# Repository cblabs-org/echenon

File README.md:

# Echenon (`v0.3.0-beta.1`)

**Open-Source Smart Bike Telemetry & FTMS Bridge for the Echelon EX-3 (Passive Tap v1)**

Echenon turns your **Echelon EX-3** indoor bike into an open, self-contained training computer and Bluetooth **FTMS (`0x1826`)** power/cadence bridge that works natively with **Zwift, MyWhoosh, TrainerRoad, Xert EBC, Wahoo SYSTM, and Garmin head units** — without cutting a single factory wire. Ride any app or instructor class while Echenon computes physics-calibrated power, relays your BLE heart-rate monitor, serves a live local web cockpit (`/ride`), and automatically syncs completed `.tcx.gz` activities to **Strava**, **Intervals.icu**, and **Wahoo Cloud**.

---

> [!IMPORTANT]
> ### 🛠️ Looking for Early Beta Builders (`v0.3.0-beta.1` — First Public Beta)
>
> We are recruiting a small cohort of capable DIY makers to build, install, and ride-test the **v1 Passive Tap Board** on their own **Echelon EX-3** bikes.
>
> **Who should join the beta:**
> - You own an **Echelon EX-3** (`ECHEX-3` / `S1001O-A03` console PCB) and want open FTMS telemetry, calibrated virtual power, and automatic cloud ride uploads.
> - You are comfortable soldering through-hole resistors/capacitors onto a `70 × 50 mm` perfboard, crimping 9-pin JST-SM and 3-pin JST connectors, verifying continuity/voltages with a multimeter, and flashing an ESP32-S3 over USB-C using PlatformIO.
> - You are willing to share structured feedback, calibration curves, and diagnostic logs via [GitHub Issues](CONTRIBUTING.md).
>
> 👉 **Start here:** Read the standalone [**v1 Beta Hardware Build & Commissioning Guide (`docs/beta-build-guide.md`)**](docs/beta-build-guide.md).

---

> [!CAUTION]
> ### ⚡ CRITICAL POWER SAFETY: `SW0` Mechanical `VIN` / `USB-C` Interlock
>
> The Echenon v1 Passive Tap Board powers the **Waveshare ESP32-S3-Nano** (`U1`) directly from the bike's `+9 V DC` supply rail (`J1` Pin 8, White) via the board's onboard **MP2322 `VIN` (6–21 V)** regulator (no external buck converter is used).
>
> **Power the ESP32-S3-Nano via bike `+9 V VIN` OR computer `USB-C` — NEVER BOTH SIMULTANEOUSLY.**
> - Always install the mandatory **`SW0` mechanical interlock switch** in series with `J1-8` (`+9 V`) to `U1 VIN`.
> - **Before plugging in USB-C:** Flip `SW0` to **USB / VIN-OFF** (or unplug the bike's 9 V wall adapter).
> - **Before powering the bike on `+9 V`:** Unplug the USB-C cable completely from `U1`, then flip `SW0` to **BIKE / VIN-ON**.
> - See [**`docs/beta-build-guide.md` (Power Interlock Checklist & §5 Pre-Power Sanity Checks)**](docs/beta-build-guide.md) before applying power.

---

## Key Capabilities (Implemented in `v0.3.0-beta.1`)

- **Non-Destructive Inline Passive Tap Harness:** Plugs inline between the EX-3's factory 9-pin JST-SM main loom (`J1 ↔ J2`) and 3-pin JST handlebar encoder loom (`J3 ↔ J4`). Every tap is high-impedance with zero internal GPIO pull-ups/pull-downs — the stock Echelon console and resistance knob continue to work normally, and unplugging the harness restores the bike to 100% stock.
- **First-Principles Calibrated Power Engine (`Physics P3r`):** Computes mechanical watts at 2 Hz from continuous ADC DMA wiper position ($\tilde{p} \in [0, 1]$) and glitch-filtered crank cadence using an electromechanical eddy-current & Kloss induction-rollover model ($R^2 = 0.9995$, $\text{RMSE} = 3.77\text{ W}$ across a 320-point empirical sweep), plus Peloton (`0–100`) braking-curve equivalence and virtual road speed.
- **Per-Bike Calibration Wizard & Live Recalibration UI:** Includes an OLS linear-endpoint **Calibration Wizard** for potentiometer end-stop tolerances, a **Recalibration UI** (`RecalibrationUI`) for fitting reference power readings (`a_scale` + $32 \times 31$ lookup matrix), and custom CSV power-table uploads.
- **Standard BLE FTMS (`0x1826`) + Heart Rate Relay (`0x180D`):**
  - Broadcasts **FTMS Indoor Bike Data (`0x2AD2`)** at 2 Hz (instantaneous power with configurable 0–10 s EMA smoothing, cadence, resistance level `1–32`, virtual speed, and heart rate) for up to 3 simultaneous BLE Central apps (Zwift, MyWhoosh, TrainerRoad, Xert EBC, Wahoo SYSTM, Garmin watches).
  - Connects as a BLE Central (`HRMClient`) to any standard BLE heart-rate strap/armband (including single-connection optical straps like the Echelon Beat `HW901`) and re-broadcasts (`HRMRepeater`) `0x180D` to the Echelon tablet app while embedding HR into FTMS and recorded sessions.
- **Autonomous Ride Recording & Multi-Sink Cloud Sync:**
  - Automatically starts recording on sustained pedalling, buffers 1 Hz anti-aliased `RideRecord` telemetry in 8 MB OPI PSRAM with 30 s LittleFS crash-recovery checkpoints (`/ride_active.bin`), and streams gzipped `.tcx.gz` files (`TCXGenerator`) with 1 Hz `<Watts>` and `<Speed>` extensions.
  - Multi-sink background `UploadQueue` (`IDataSource`) with `BLEManager::ScanInhibit` radio coexistence pushes completed sessions to **Strava** (`StravaUploader`, BYOA OAuth 2.0 — setup guide includes a one-click `/icon-512.png` download of the Concept A app icon, also at [`docs/assets/echenon-icon-512.png`](docs/assets/echenon-icon-512.png)), **Intervals.icu** (`IntervalsIcuUploader`, API key), and **Wahoo Cloud** (`WahooUploader`, BYOA OAuth 2.0), plus optional LittleFS `.ride.gz` persistence (`RidePersistence`).
- **Live Web Cockpit (`/ride`), Portal & JSON-RPC MCP Tools (`/api/mcp`):**
  - **Standalone `/ride` page** (installable as a mobile/tablet split-screen PWA via `/manifest.json` with Concept A `"Telemetry Dial"` icons `/icon-192.png`, `/icon-512.png`, `/favicon.svg`, and `/favicon.ico`) with 2 Hz WebSocket telemetry (`/ws/echenon/live`), rolling 5-minute power chart, HR zones, session start/pause/resume/stop controls, and multi-sink sync prompts (`"Save to device and sync to connected apps"`), backed by `SessionOverlay` REST routes (`/api/session/*`, `/api/upload/*`, `/api/strava/*`, `/api/intervals/*`, `/api/wahoo/*`).
  - **Main Web Portal (`http://echenon.local`)** with live dashboard, Calibration Wizard, Power Tuning, Stored Rides history (`/stored_rides.js`), and Diagnostics event/run viewer (`DiagnosticsRoutes`), protected by **`AuthManager` portal authentication** (`WO-09.1`).
  - **Model Context Protocol (`POST /api/mcp` via `IMCPContributor`):** Exposes structured JSON-RPC tools (`echenon_get_telemetry`, `echenon_calibration`, `echenon_recalibration`, `echenon_upload_power_table`, `echenon_set_ftms_smoothing`, plus `echenon_rig_status` and `echenon_rig_command` when built with `-DWITH_CALIBRATION_RIG` — migrated 100% off legacy HTTP endpoints).

---

## Shopping List & 5-Step Quick Start (`~USD $25–$35`)

### Bill of Materials Summary (v1 Passive Tap Board)

Full circuit schematics, pin-by-pin wire colour tables, and multimeter checklists are in [**`docs/beta-build-guide.md`**](docs/beta-build-guide.md):

| Ref | Part | Qty | Value / Spec | Role |
|---|---|---|---|---|
| `U1` | **Waveshare ESP32-S3-Nano** | 1 | `ESP32-S3R8` (16 MB Flash / 8 MB OPI PSRAM, onboard MP2322 `VIN` 6–21 V regulator) | Main MCU (**no external `U3` buck converter needed**) |
| `SW0` | **Mechanical Interlock Switch** | 1 | SPDT slide/toggle switch rated ≥ 1 A @ 12 V DC (+ optional `D1` `1N5819`/`SS14` Schottky diode) | Series disconnect on `J1-8` (`+9 V`) to `U1 VIN` (**`VIN` OR `USB-C`, never both**) |
| `RS1–RS3` | **22 kΩ Resistors** | 3 | `22 kΩ`, 1% metal film, 1/4 W | High-Z series taps on potentiometer lines (`GPIO 1, 2, 3`) |
| `RS4–RS8` | **4.7 kΩ Resistors** | 5 | `4.7 kΩ`, 1% metal film, 1/4 W | Series protection & RC filter input for cadence (`GPIO 4, 5`) and encoder (`GPIO 8, 9, 10`) |
| `R1a, R2a` | **30 kΩ Resistors** | 2 | `30 kΩ`, 1% metal film, 1/4 W | Upper leg of ÷4 motor-sense dividers (`GPIO 6, 7`) |
| `R1b, R2b` | **10 kΩ Resistors** | 2 | `10 kΩ`, 1% metal film, 1/4 W | Lower leg to `GND` of ÷4 motor-sense dividers (`GPIO 6, 7`) |
| `C1 ×5` | **100 nF Ceramic Capacitors** | 5 | `100 nF` (`0.1 µF`), X7R, ≥ 16 V | Low-pass filter (~338 Hz) & ADC charge reservoir from **ESP32 GPIO side** of `RS4–RS8` to `GND` (`GPIO 4, 5, 8, 9, 10`) |
| `J1 / J2` | **JST-SM 9-Pin Socket + Plug** | 1 pair | 9-pin JST-SM female receptacle (`J1`) + male plug (`J2`) | Main frame-to-console inline pass-through |
| `J3 / J4` | **JST 3-Pin Socket + Plug** | 1 pair | 3-pin JST female receptacle (`J3`) + male plug (`J4`) | Handlebar resistance knob encoder inline pass-through |
| `J5` + Board | **Headers, Perfboard & Wire** | 1 set | `2× 15-pin` `2.54 mm` female socket strips, `70 × 50 mm` FR-4 perfboard, `22 AWG` wire | Carrier board fitting inside the EX-3 console housing |

### Quick Start in 5 Steps

1. **Assemble & Bench-Check the Harness (`U1` Unseated):**
   Follow [**`docs/beta-build-guide.md` (§2–§5)**](docs/beta-build-guide.md) to solder the pass-through looms, resistor/capacitor taps, and `SW0` interlock onto the `70 × 50 mm` perfboard. Complete every unpowered continuity check and live voltage check **before** seating the ESP32-S3-Nano (`U1`) into `J5`.
2. **Clone Repository & Initialize Submodule:**
   ```bash
   git clone --recurse-submodules https://github.com/cblabs-org/echenon.git
   cd echenon
   ```
   *(Note: Echenon builds on the public [`cblabs-org/esp32-app-foundation`](https://github.com/cblabs-org/esp32-app-foundation) submodule (`v1.0.0-beta.2`) under `framework/`.)*
3. **Isolate `VIN` (`SW0` → USB) & Flash Over USB-C:**
   Verify `SW0` is in the **USB / VIN-OFF** position (or the board is unplugged from the bike), seat `U1` into `J5`, connect a USB-C data cable, and flash both the firmware and LittleFS portal image:
   ```bash
   pio run -e ex3-waveshare-nano -t upload
   pio run -e ex3-waveshare-nano -t uploadfs
   ```
4. **WiFi Onboarding & Portal Authentication:**
   Connect to the **`Echenon`** setup WiFi AP (`http://192.168.4.1`), join your 2.4 GHz home WiFi, then open **`http://echenon.local`** and set your administrator password (`AuthManager` protects all configuration, calibration, and ride management routes).
5. **Install in Console, Calibrate & Ride:**
   Unplug the USB-C cable completely, connect `J1 ↔ J2` and `J3 ↔ J4` inline inside the EX-3 console shell, flip `SW0` to **BIKE / VIN-ON**, and power on the bike. Run the **Level Mapping Calibration Wizard** in the portal (`Apps → Level Mapping`), pair your BLE heart-rate monitor (`Bluetooth` tab), configure your connected apps (`Apps → Strava` — using `/icon-512.png` or [`docs/assets/echenon-icon-512.png`](docs/assets/echenon-icon-512.png) when Strava prompts for an app icon — plus `Intervals.icu` and `Wahoo Cloud`), and open **`http://echenon.local/ride`** (or install it as a PWA) or pair `Echenon-XXXX` in Zwift / TrainerRoad / MyWhoosh!

---

## Known Beta Limitations & Roadmap (`v1` → `v2`)

1. **Passive Read-Only Tap in `v1` (No ERG / Active Resistance Control Yet):**
   - The `v1` board is strictly an inline passive observer. You adjust resistance manually with the red handlebar knob while Echenon broadcasts live watts, cadence, resistance level, and heart rate over BLE FTMS (`0x1826`). Closed-loop motor control (`ERG` mode, FTMS Control Point `0x2AD9`, HR-zone auto-resistance, and console-off standalone mode) is planned for the **v2 Active Intercept (MITM) Board**.
2. **`WITH_OTA` Disabled in `v0.3.0-beta.1` (USB-C Updates Only):**
   - Over-the-air firmware updating (`WITH_OTA`) is intentionally disabled in `v0.3.0-beta.1` while upstream framework OTA boot-guard hardening is finalised. All firmware and LittleFS updates during beta are performed over **USB-C with `SW0` flipped to `USB / VIN-OFF`**.
3. **Stock Console Motor Control & Power-Off Best Practice:**
   - Because the stock EX-3 console drives the motor directly in `v1`, stock console firmware quirks remain unchanged (including the stock EX-3 behaviour where unplugging power while parked at a high resistance level can misindex the console's step counter). Echenon detects out-of-range potentiometer travel (`RunawayDetector`) and logs a portal alert, but passive hardware cannot cut motor power. **Best practice:** return the knob to **Level 1** before unplugging the bike.
4. **Verified Bike Model Scope:**
   - Verified on the **Echelon EX-3** (`ECHEX-3` / `S1001O-A03` console PCB). Other Echelon Connect models (EX-1, EX-4s, EX-5, Sport) may share similar harness pinouts but are currently untested — hardware reports and pull requests are welcome!

---

## Documentation Index

| Document | Description |
|---|---|
| [**`docs/beta-build-guide.md`**](docs/beta-build-guide.md) | **Start Here:** Standalone v1 Passive Tap Board BOM, wiring tables, schematics, multimeter checks, USB-C flashing & calibration guide |
| [**`hardware/ex3-waveshare-nano/pcb/`**](hardware/ex3-waveshare-nano/pcb/README.md) | **KiCad 10 PCB Package & Printable Schematics:** [Printable v1 Schematic PDF](hardware/ex3-waveshare-nano/pcb/v1-passive-tap/echenon_v1_passive_tap.pdf), [v1 PCB Layout PDF](hardware/ex3-waveshare-nano/pcb/v1-passive-tap/echenon_v1_passive_tap_pcb.pdf), [v1 Gerbers ZIP](hardware/ex3-waveshare-nano/pcb/gerbers/v1-passive-tap/echenon_v1_passive_tap_gerbers.zip) & Carvera Air CAM runbook |
| [**`SPEC.md`**](SPEC.md) | Canonical Echenon system & firmware specification (v1 Passive & provisional v2 Active architecture) |
| [**`docs/hardware_specification.md`**](docs/hardware_specification.md) | Detailed circuit engineering reference, oscilloscope evidence, impedance analysis & v2 MITM draft notes |
| [**`docs/ex3_specification.md`**](docs/ex3_specification.md) | Echelon EX-3 stock hardware teardown, connector pinouts, actuator cam & sensor electrical profiles |
| [**`docs/power-physics-model.md`**](docs/power-physics-model.md) | First-principles derivation & 320-point empirical verification of the `Physics P3r` eddy-current power model |
| [**`docs/data-sinks.md`**](docs/data-sinks.md) | Multi-sink `UploadQueue` architecture and setup guide for Strava, Intervals.icu, and Wahoo Cloud |
| [**`docs/diagnostics.md`**](docs/diagnostics.md) | PSRAM ring-buffer `DiagnosticsModule` event types and `/api/echenon/events` REST API |
| [**`docs/run-data-persistence.md`**](docs/run-data-persistence.md) | Optional LittleFS `.ride.gz` binary ride storage (`RidePersistence`) and CSV export routes |
| [**`docs/use_case_analysis.md`**](docs/use_case_analysis.md) | Operating scenarios (`UC1`–`UC6`) across Echelon classes, Zwift/FTMS apps, and free rides |
| [**`docs/upstream-ble-without-wifi-assessment.md`**](docs/upstream-ble-without-wifi-assessment.md) | Assessment & upstream issue draft for BLE peripheral/central operation without WiFi STA |
| [**`CONTRIBUTING.md`**](CONTRIBUTING.md) | Beta bug reporting guidelines, secret-scrubbing checklist, build environments & developer workflow |
| [**`CHANGELOG.md`**](CHANGELOG.md) | Release history and `v0.3.0-beta.1` capability summary |
| [**`LICENSE`**](LICENSE) | Apache License 2.0 and third-party MIT attribution notices |

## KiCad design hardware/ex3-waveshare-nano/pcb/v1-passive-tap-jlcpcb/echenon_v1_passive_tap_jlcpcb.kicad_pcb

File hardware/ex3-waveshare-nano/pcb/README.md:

# Echenon PCB Fabrication Package (`ex3-waveshare-nano`)

**KiCad 10** PCB projects, **Makera Carvera Air** home-CNC bundles, and **JLCPCB 2-Layer SMD PCBA** turnkey assembly bundles for the Echenon hardware ([beta-build-guide.md](../../../docs/beta-build-guide.md), [hardware_specification.md](../../../docs/hardware_specification.md), [board.h](../board.h)).

- **Deliverables A & B (Carvera Air Home CNC):** **100% single-sided bottom-copper (`B.Cu`)** through-hole layouts — zero copper via rivets, zero double-sided board flips, and zero inaccessible solder joints beneath `J5` headers.
- **Deliverable C (JLCPCB 2-Layer SMD PCBA — Hybrid Carrier):** **2-layer FR-4 (`F.Cu` + solid `B.Cu` ground plane)** layout where JLCPCB factory-populates all **18 surface-mount passives + Schottky diode** using **100% \$0-setup JLCPCB Basic Parts**, leaving only the `2.54 mm` headers/pigtails (`J1–J4`, `SW0`, `U1` socket) for quick bench soldering.

---

## 1. Repository Layout

| Path | Purpose | Dimensions | Status |
|---|---|---|---|
| [generate_pcbs.py](generate_pcbs.py) | Deterministic KiCad 10 S-expression generator + `kicad-cli` ERC/DRC, Gerber, BOM/CPL, 3D PNG, SVG & PDF runner | — | Verified |
| [coupon/](coupon/) | **Deliverable A:** Carvera Air calibration test coupon (`carvera_calibration_coupon.kicad_*`, [schematic PDF](coupon/carvera_calibration_coupon.pdf), [PCB PDF](coupon/carvera_calibration_coupon_pcb.pdf)) | `25 × 20 mm` | ERC=0, DRC=0 |
| [v1-passive-tap/](v1-passive-tap/) | **Deliverable B:** Carvera Air v1 Passive Tap Board (`echenon_v1_passive_tap.kicad_*`, [schematic PDF](v1-passive-tap/echenon_v1_passive_tap.pdf), [PCB PDF](v1-passive-tap/echenon_v1_passive_tap_pcb.pdf)) | `70 × 50 mm` | ERC=0, DRC=0 |
| [v1-passive-tap-jlcpcb/](v1-passive-tap-jlcpcb/) | **Deliverable C:** JLCPCB 2-Layer SMD PCBA v1 Passive Tap Board (`echenon_v1_passive_tap_jlcpcb.kicad_*`, [schematic PDF](v1-passive-tap-jlcpcb/echenon_v1_passive_tap_jlcpcb.pdf), [PCB PDF](v1-passive-tap-jlcpcb/echenon_v1_passive_tap_jlcpcb_pcb.pdf)) | `70 × 50 mm` | ERC=0, DRC=0, SMD=18 |
| [gerbers/coupon/](gerbers/coupon/) | Ready-to-mill Gerbers, Excellon drills, [`carvera_calibration_coupon_gerbers.zip`](gerbers/coupon/carvera_calibration_coupon_gerbers.zip), SVGs | `25 × 20 mm` | 2 drills (`0.9`, `1.0 mm`) |
| [gerbers/v1-passive-tap/](gerbers/v1-passive-tap/) | Ready-to-mill Gerbers, Excellon drills, [`echenon_v1_passive_tap_gerbers.zip`](gerbers/v1-passive-tap/echenon_v1_passive_tap_gerbers.zip), SVGs | `70 × 50 mm` | 2 drills (`0.9`, `1.0 mm`) |
| [gerbers/v1-passive-tap-jlcpcb/](gerbers/v1-passive-tap-jlcpcb/) | Turnkey JLCPCB bundle: [`echenon_v1_passive_tap_jlcpcb_gerbers.zip`](gerbers/v1-passive-tap-jlcpcb/echenon_v1_passive_tap_jlcpcb_gerbers.zip), [`_bom.csv`](gerbers/v1-passive-tap-jlcpcb/echenon_v1_passive_tap_jlcpcb_bom.csv), [`_cpl.csv`](gerbers/v1-passive-tap-jlcpcb/echenon_v1_passive_tap_jlcpcb_cpl.csv), [3D Top PNG](gerbers/v1-passive-tap-jlcpcb/echenon_v1_passive_tap_jlcpcb_3d_top.png), [3D Bottom PNG](gerbers/v1-passive-tap-jlcpcb/echenon_v1_passive_tap_jlcpcb_3d_bottom.png) | `70 × 50 mm` | 2-Layer + Economic PCBA |

---

## 2. Carvera Air CNC Design Rules (Built Into Both Boards)

- **Copper Layer:** `B.Cu` only (no `F.Cu` tracks, no vias).
- **Minimum Track Width:** `0.50 mm` signals (`0.60–0.90 mm` for motor sense pass-throughs, `GND`, and `+9 V`).
- **Minimum Copper Clearance:** `0.45 mm` everywhere (sized for `0.2 mm 30°` V-bits with 2–3 isolation passes).
- **Standardized Tooling (Only 2 Drill Sizes):**
  - `T1 = 0.90 mm`: Axial resistors (`RS1–RS8`, `R1a/b`, `R2a/b`), Schottky diode (`D1`), ceramic capacitors (`C1_1–C1_5`).
  - `T2 = 1.00 mm`: Waveshare ESP32-S3-Nano socket headers (`J5` / `U1`), pigtail solder pads (`J1–J4`), and `SW0` interlock pins.
  - `0.80 mm` corn endmill (`Edge.Cuts`): Board perimeter, corner `M2.5` mounting holes (`2.70 mm` dia), and pigtail strain-relief tie holes (`2.20 mm` dia) — milled automatically on the contour pass with zero extra drill bits.

---

## 3. Deliverable A: Calibration Coupon (`25 × 20 mm`)

Mill the coupon first in the corner of a **single-sided blank** (`100 × 150 mm`) to dial in your V-bit cut depth and drill fit before cutting the full `70 × 50 mm` board:

- Tests one `÷4` motor-sense divider cell (`R_DIV1 30 kΩ`, `R_DIV2 10 kΩ`) + `C_FILT1 100 nF` cap + `J_LOOM1` (`1×2` pigtail pads) + `J_TEST1` (`1×3` Nano socket strip) + one `2.2 mm` strain-relief hole.
- **Check after milling:**
  1. Confirm `0.50 mm` & `1.00 mm` copper traces are crisp with clean isolation channels and no copper whiskers.
  2. Test-fit your `2.54 mm` female socket strip into `J_TEST1` (`1.00 mm` holes), `1/4 W` axial resistor leads into `R_DIV1` (`0.90 mm` holes), and stripped `22 AWG` JST pigtail wire into `J_LOOM1` (`1.00 mm` holes).

---

## 4. Deliverable B: Echenon v1 Passive Tap Board (`70 × 50 mm`)

Matches the DR-1 frozen schematic in [beta-build-guide.md](../../../docs/beta-build-guide.md) and [board.h](../board.h):

- **Top-Side Component Placement (`F.SilkS`):**
  - `J4` (Console) ↔ `J3` (Resistance Knob), 3-pin JST pigtail banks (`1: Black ENC_CHA`, `2: Orange/Yellow ENC_VCC`, `3: Red ENC_CHB`).
  - `J2` (Console) ↔ `J1` (Bike Frame), 9-pin JST-SM pigtail banks (`1: Red MOT+`, `2: Black MOT−`, `3: Yellow POT_HI`, `4: Blue POT_WIPER`, `5: Green POT_LO`, `6: Orange CAD`, `7: Grey CAD_RTN`, `8: White +9V`, `9: Brown GND`).
  - **Strain Relief:** Loop a small nylon zip-tie through the `2.2 mm` holes beside `J1/J2` and `J3/J4` around each pigtail cable jacket so pulling the plugs never stresses the solder joints.
  - **`SW0` Physical USB-C Blocker (`x = 4.80 mm`):** Mount a `2-pin` header or socket/jumper block straddling the USB-C port entrance of `U1`. When the `+9 V` bridge jumper is installed across `SW0`, it **physically blocks insertion of a USB-C cable**.
  - **`D1` (`1N5819` Schottky Diode):** Bridges vertically over the bottom `A0–A3` tracks (`Pad 1` square cathode toward `U1` `VIN`, `Pad 2` round anode toward `SW0`). Match the diode silver/white cathode band to the square pad!
  - **Reserved Pins Left Unconnected:** `U1` `D8` (`GPIO 17`), `D1/TX1` (`GPIO 43`), `D0/RX0` (`GPIO 44`).
- **Schematics & Off-Board Reference Circuitry:** Both schematics use official KiCad 10 IEC symbols (`Device:R`, `Device:C`, `Device:D_Schottky`, `Switch:SW_SPST`, `Connector_Generic:Conn_01x*`, `power:GND`) with continuous wired dividers, RC filters, and harnesses. [echenon_v1_passive_tap.kicad_sch](v1-passive-tap/echenon_v1_passive_tap.kicad_sch) also includes dashed off-board EX-3 bike and stock console reference blocks (`M1`, `RV1`, `SW_CAD1`, `PS1`, `ENC1`, `CON1`) marked `on_board no`, `in_bom no`, and `in_pos_files no` so end-to-end signal flow is documented without entering the PCB or BOM.

---

## 5. Makera CAM & Carvera Air Production Runbook

### Step 1: Stock Setup
1. Secure a clean **single-sided copper-clad blank (`100 × 150 mm`)** **copper-side UP** onto your Carvera Air wasteboard/sub-spoiler using flat double-sided tape across the full underside (essential so the board does not vibrate or lift during V-bit isolation).
2. Register the lower-left corner against the L-bracket origin.
3. Put **bit collars** on your 4 tools (matching your Makera PCB Fabrication Pack):
   - **Isolation:** `1/8"` `0.2 mm 30°` V-bit (or `0.1 mm 60°` V-bit)
   - **Drill 1:** `0.90 mm` PCB drill bit
   - **Drill 2:** `1.00 mm` PCB drill bit
   - **Contour / Cutout:** `0.80 mm` corn endmill

### Step 2: Import & Mirror in Makera CAM (CRITICAL FOR SINGLE-SIDED `B.Cu`)
1. Open **Makera CAM** → create a **3-Axis Project**.
2. Click **Import PCB** and select the unzipped Gerbers + `.drl` files from [gerbers/coupon/](gerbers/coupon/) or [gerbers/v1-passive-tap/](gerbers/v1-passive-tap/) (`*-bottom_layer.gbl`, `*-B_Mask.gbs`, `*-Edge_Cuts.gm1`, `*-PTH.drl`).
3. **CRITICAL — Mirror Together Before Generating Toolpaths:**
   - Standard KiCad `B.Cu` Gerbers and `.drl` files are exported in **top-down X-ray coordinates**, whereas your single-sided copper blank sits **copper-side UP** on the Carvera bed.
   - Select **all imported PCB layers together** (`B.Cu`, `B.Mask`, `Edge.Cuts`, `PTH.drl`) → **Adjust Object → Mirror (Horizontal / across Y-axis around Stock Center)**.
   - **Visual Sanity Check (Do Not Skip!):** Compare the Makera CAM workspace view against the mirrored bottom-copper preview SVG:
     - Coupon: [gerbers/coupon/carvera_calibration_coupon_bottom_copper.svg](gerbers/coupon/carvera_calibration_coupon_bottom_copper.svg) (`J_LOOM1` on top-right, strain-relief hole on top-right corner).
     - v1 Board: [gerbers/v1-passive-tap/echenon_v1_passive_tap_bottom_copper.svg](gerbers/v1-passive-tap/echenon_v1_passive_tap_bottom_copper.svg) (**`SW0` on the RIGHT**, **`J1/J2` 9-pin bank on the TOP-LEFT**, **`J3/J4` 3-pin bank on the TOP-RIGHT**, and `ECHENON v1 B.Cu` text readable left-to-right).

### Step 3: Toolpaths & Milling Parameters
1. **Isolation Routing (`*-bottom_layer.gbl`):**
   - Bit: `0.2 mm 30°` V-bit (`12,000–13,000 RPM`, feed `150–250 mm/min`, plunge `60 mm/min`).
   - Cut depth: `-0.08 mm` to `-0.10 mm` (`1 oz` copper is `0.035 mm` thick; `0.08 mm` cleanly cuts through copper + minor surface variation without digging deep into substrate).
   - Isolation passes: **2–3 passes** (`~0.25–0.35 mm` total moat width; our `0.45 mm` minimum DRC clearance gives plenty of margin).
2. **Drilling (`*-PTH.drl`):**
   - `T1 = 0.90 mm` (`10,000 RPM`, plunge `120–150 mm/min`, depth `-1.85 mm` for `1.5 mm` FR-4/FR-1 blank).
   - `T2 = 1.00 mm` (same speed/feed/depth).
3. **Contour & Mounting/Strain-Relief Holes (`*-Edge_Cuts.gm1`):**
   - Bit: `0.80 mm` corn endmill (`10,000–12,000 RPM`, `2–3` step-downs to `-1.85 mm` depth, feed `150–200 mm/min`).
   - Add **4 small holding tabs** (`1.5 mm` wide × `0.6 mm` high) on the outer board rectangle (not inside the mounting/strain-relief circles).

### Step 4: Carvera Controller Execution & Safety
1. Enable **Auto-Leveling (`G32` wireless Z-probe mesh)** across the PCB bounding box (e.g., `5 × 4` or `7 × 5` grid points) before cutting traces.
2. Follow **Carvera Controller** prompts during **`M6` Quick Tool Changes** (each bit swap automatically runs the tool-length offset setter).
3. **Dust Safety (especially for FR-4 blanks):**
   - Keep the Carvera Air enclosure closed and run vacuum extraction throughout the cut.
   - Wear an N95/P100 mask when opening the lid, **never** use compressed air, and wipe the finished board and bed clean with a damp paper towel or isopropyl alcohol (IPA) wipe.
4. *(Optional)* **UV Solder Mask (Final Bike Board Only):** Skip UV mask on your first test board so every trace is easy to inspect and probe. For the final bike-installed board, roll a thin coat of UV solder mask onto the copper side, cure under the `365 nm` lamp, and run Makera CAM's pad-clearing pass from `*-B_Mask.gbs` using the spring-loaded mask removal bit.

---

## 6. Post-Mill Pre-Power Verification (With `U1` Unseated!)

Before inserting the **Waveshare ESP32-S3-Nano** (`U1`) into `J5`:
1. Visually inspect all isolation moats under bright light/magnifier and scrub lightly with Scotch-Brite/IPA to remove any fine copper burrs.
2. Buzz out continuity on all 12 straight pass-through pins (`J1-1..9 ↔ J2-1..9`, `J3-1..3 ↔ J4-1..3`).
3. Verify **zero continuity (open circuit)** between adjacent pads and between `+9 V` (`J1-8`), `VIN` (`U1-30`), and `GND` (`J1-9`).
4. Solder `RS1–RS8`, `R1a/b`, `R2a/b`, `C1_1–C1_5`, `D1`, `SW0`, `J5` headers, and `J1–J4` pigtails.
5. **Interlock Check:** With `U1` still unseated, apply `+9 V` to `J1-8`/`J1-9`:
   - `SW0` **OPEN (USB position):** `0.0 V` at `U1` `VIN` (`Pad 30`).
   - `SW0` **BRIDGED (BIKE position):** `~8.6–8.7 V` at `U1` `VIN` (`Pad 30`, accounting for `D1` `~0.35 V` Schottky drop), and USB-C port physically blocked.
6. Proceed with [beta-build-guide.md §5–§7](../../../docs/beta-build-guide.md) to seat `U1` and commission on the EX-3.

---

## 7. Deliverable C: JLCPCB 2-Layer SMD PCBA Edition (`70 × 50 mm`)

[v1-passive-tap-jlcpcb/](v1-passive-tap-jlcpcb/) implements the identical DR-1 frozen circuit as a **2-layer FR-4 (`1.6 mm`) Hybrid SMD Carrier**:

- **2-Layer Signal Integrity:** Top-side (`F.Cu`) `0805`/`SMA` SMD placement over an unbroken thermal-relieved **`B.Cu` `GND` ground plane** with dedicated ground vias right beside every `100 nF` RC filter capacitor (`C1_1–C1_5`) and `÷4` divider leg (`R1b`, `R2b`).
- **Optical & Mechanical Features:** 3 asymmetric `1.0 mm` optical fiducials (`FID1–FID3`, `>= 5 mm` from edges), 4 corner `M2.5` (`2.70 mm` NPTH) mounting holes (`MH1–MH4`), and 3 `2.20 mm` NPTH zip-tie strain-relief holes (`SR1–SR3`). All 18 SMD components sit well inside JLCPCB's `5 mm` conveyor rail margin.
- **100% JLCPCB Basic Parts (\$0 Feeder Setup Fee on Economic PCBA):**

| Designators | Value / Spec | Package | MPN | JLCPCB Part # | Tier | Qty |
|---|---|---|---|---|---|---|
| `RS4–RS8` | `4.7 kΩ` ±1% 1/8W | `0805` | `0805W8F4701T5E` | **`C17673`** | Basic | 5 |
| `R1b, R2b` | `10 kΩ` ±1% 1/8W | `0805` | `0805W8F1002T5E` | **`C17414`** | Basic | 2 |
| `RS1–RS3` | `22 kΩ` ±1% 1/8W | `0805` | `0805W8F2202T5E` | **`C17560`** | Basic | 3 |
| `R1a, R2a` | `30 kΩ` ±1% 1/8W | `0805` | `0805W8F3002T5E` | **`C17621`** | Basic | 2 |
| `C1_1–C1_5` | `100 nF` 50V X7R | `0805` | `CL21B104KBCNNNC` | **`C49678`** | Basic | 5 |
| `D1` | `SS14` 40V 1A Schottky | `SMA (DO-214AC)` | `SS14` | **`C2480`** | Basic | 1 |

### JLCPCB Ordering Steps
1. Go to [jlcpcb.com](https://jlcpcb.com) → **Order Now** → upload [`echenon_v1_passive_tap_jlcpcb_gerbers.zip`](gerbers/v1-passive-tap-jlcpcb/echenon_v1_passive_tap_jlcpcb_gerbers.zip).
2. Keep standard 2-layer defaults (`FR-4`, `2 Layers`, `1.6 mm` thickness, `1 oz` copper, `HASL (with lead)` or `LeadFree HASL` / `ENIG`, `5 pcs`).
3. Scroll down and toggle **PCB Assembly** → **ON**:
   - **PCBA Type:** `Economic`
   - **Assembly Side:** `Top Side`
   - **PCBA Qty:** `2` (or `5` to populate the entire batch)
4. Click **Next**, then upload:
   - **BOM File:** [`echenon_v1_passive_tap_jlcpcb_bom.csv`](gerbers/v1-passive-tap-jlcpcb/echenon_v1_passive_tap_jlcpcb_bom.csv)
   - **CPL File:** [`echenon_v1_passive_tap_jlcpcb_cpl.csv`](gerbers/v1-passive-tap-jlcpcb/echenon_v1_passive_tap_jlcpcb_cpl.csv)
5. **DFM / Polarity Sanity Check (10 seconds):** On JLCPCB's 2D/3D component placement preview, confirm that **`D1` (`SS14`)** has its cathode band facing **LEFT** over the **`K`** silkscreen bar (matching [echenon_v1_passive_tap_jlcpcb_3d_top.png](gerbers/v1-passive-tap-jlcpcb/echenon_v1_passive_tap_jlcpcb_3d_top.png)). If a reel change ever flips `D1`, click `D1` in the preview and rotate `180°`.
6. **Bench Finish Upon Arrival (~5 minutes):** Solder the `2×15` `2.54 mm` female socket strips (`U1`), the `2-pin` USB-C blocker header/jumper (`SW0`), and either `2.54 mm` headers or pre-wired JST pigtails (`J1–J4`). Run the `SW0` interlock check in §6 Step 5 before seating your Waveshare ESP32-S3-Nano!

---

## 8. Regenerating After Changes

```bash
python3 hardware/ex3-waveshare-nano/pcb/generate_pcbs.py
```

The script regenerates all three KiCad 10 projects (`coupon`, `v1-passive-tap`, `v1-passive-tap-jlcpcb`), runs headless `kicad-cli sch erc` and `kicad-cli pcb drc --schematic-parity --severity-all` (with automatic `B.Cu` zone filling), verifies 1-to-1 BOM/CPL designator parity, and rebuilds all Gerbers, drill files, CSVs, 3D PNG renders, SVGs, printable PDFs, and `.zip` archives.

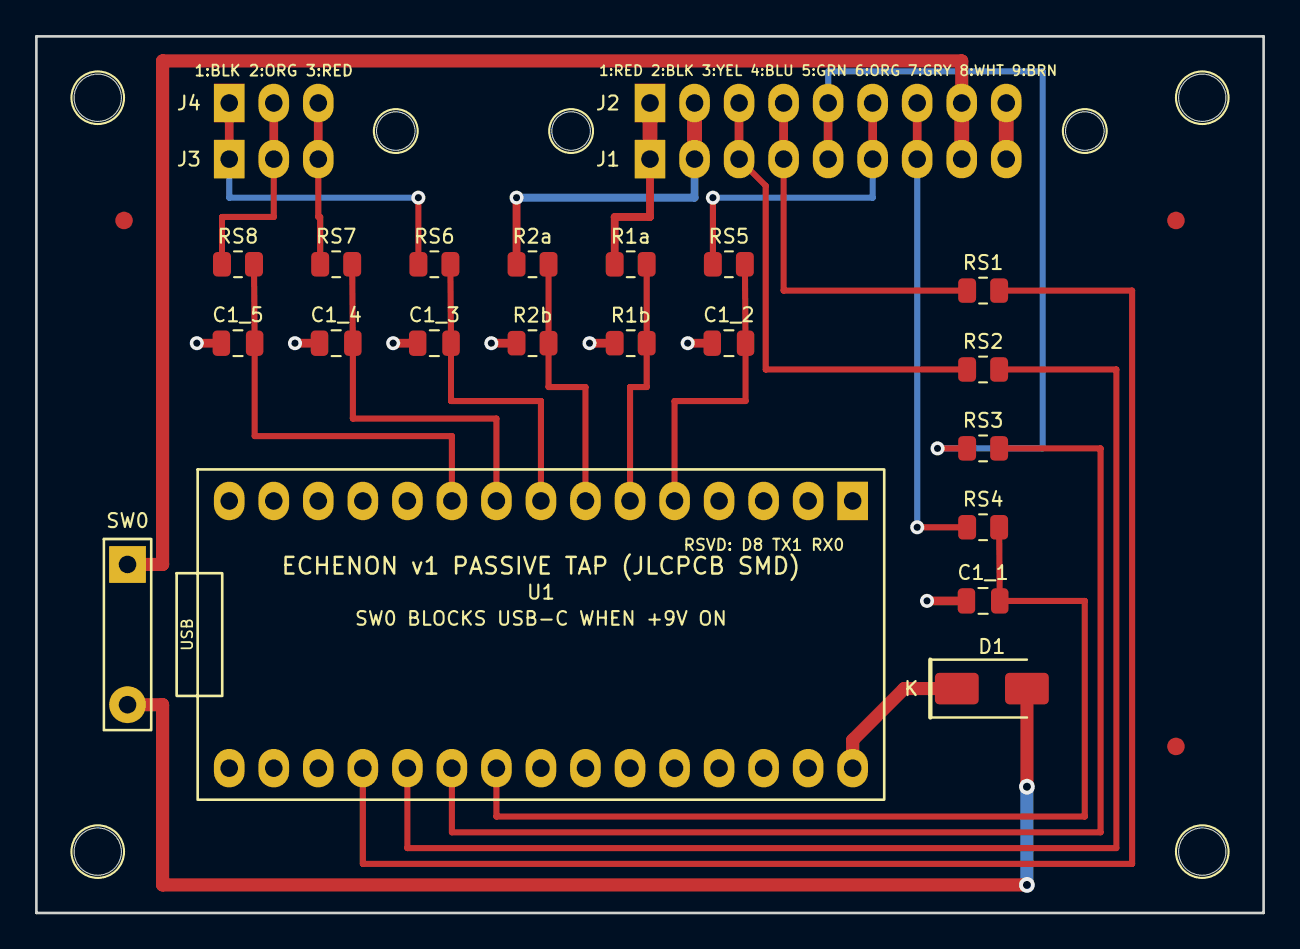
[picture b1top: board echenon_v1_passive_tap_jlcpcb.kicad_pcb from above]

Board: 2 copper layers, 70.0 x 50.0 mm, 34 parts (0 on the bottom side), 24 nets.

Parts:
C1_1, C1_2, C1_3, C1_4, C1_5: 100nF; C_0805_2012Metric
D1: SS14; D_SMA
FID1, FID2, FID3: Fiducial; Fiducial_1mm_Mask2mm
J1: JST_SM_9P_BIKE; Header_Pigtail_1x09_P2.54mm
J2: JST_SM_9P_CONSOLE; Header_Pigtail_1x09_P2.54mm
J3: JST_3P_KNOB; Header_Pigtail_1x03_P2.54mm
J4: JST_3P_CONSOLE; Header_Pigtail_1x03_P2.54mm
MH1, MH2, MH3, MH4: M2.5_2.7mm; NPTH_2.7mm
R1a, R2a: 30k; R_0805_2012Metric
R1b, R2b: 10k; R_0805_2012Metric
RS1, RS2, RS3: 22k; R_0805_2012Metric
RS4, RS5, RS6, RS7, RS8: 4.7k; R_0805_2012Metric
SR1, SR2, SR3: ZIP_2.2mm; NPTH_2.2mm
SW0: VIN_USBC_INTERLOCK; Interlock_USB_Blocker_2P_THT
U1: Waveshare_ESP32-S3-Nano; Waveshare_ESP32_S3_Nano_Socket_THT

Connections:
/GPIO1_POT_WIPER: RS1.2, U1.19
/GPIO2_POT_HI: RS2.2, U1.20
/GPIO3_POT_LO: RS3.2, U1.21
/GPIO4_CAD_RTN: C1_1.2, RS4.2, U1.22
/GPIO5_CADENCE: C1_2.2, RS5.2, U1.5
/GPIO6_MOT_P: R1a.2, R1b.2, U1.6
/GPIO7_MOT_N: R2a.2, R2b.2, U1.7
/GPIO8_ENC_A: C1_3.2, RS6.2, U1.8
/GPIO9_ENC_B: C1_4.2, RS7.2, U1.9
/GPIO10_ENC_VCC: C1_5.2, RS8.2, U1.10
/NET_J1_1_MOT_P: J1.1, J2.1, R1a.1
/NET_J1_2_MOT_N: J1.2, J2.2, R2a.1
/NET_J1_3_POT_HI: J1.3, J2.3, RS2.1
/NET_J1_4_POT_WIPER: J1.4, J2.4, RS1.1
/NET_J1_5_POT_LO: J1.5, J2.5, RS3.1
/NET_J1_6_CADENCE: J1.6, J2.6, RS5.1
/NET_J1_7_CAD_RTN: J1.7, J2.7, RS4.1
/NET_J1_8_V9_RAW: J1.8, J2.8, SW0.1
/NET_J3_1_ENC_A: J3.1, J4.1, RS6.1
/NET_J3_2_ENC_VCC: J3.2, J4.2, RS8.1
/NET_J3_3_ENC_B: J3.3, J4.3, RS7.1
/NET_SW0_D1: D1.2, SW0.2
/NET_VIN_9V: D1.1, U1.30
GND: C1_1.1, C1_2.1, C1_3.1, C1_4.1, C1_5.1, J1.9, J2.9, R1b.1, R2b.1, U1.4, U1.29

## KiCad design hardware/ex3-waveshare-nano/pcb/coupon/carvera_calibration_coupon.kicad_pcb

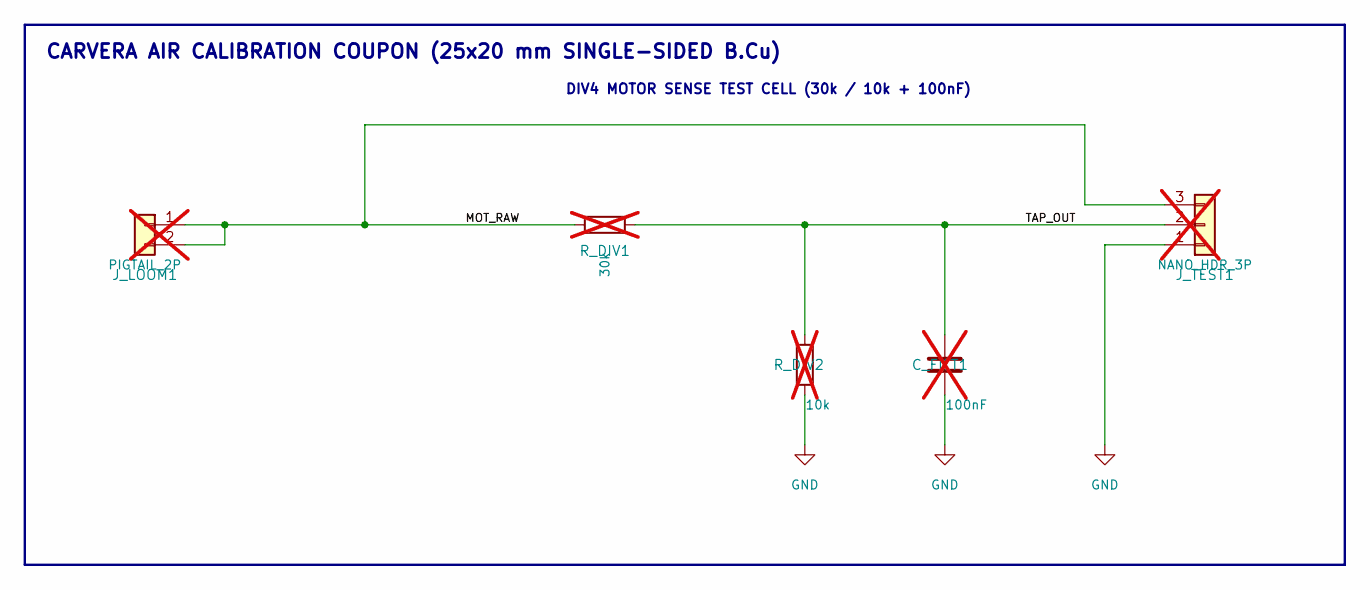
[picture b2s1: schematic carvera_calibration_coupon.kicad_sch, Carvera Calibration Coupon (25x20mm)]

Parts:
C_FILT1: 100nF; C_Disc_P5.08mm_CNC; not fitted
J_LOOM1: PIGTAIL_2P; Pigtail_1x02_P2.54mm_CNC; not fitted
J_TEST1: NANO_HDR_3P; NanoSocket_1x03_P2.54mm_CNC; not fitted
R_DIV1: 30k; R_Axial_P7.62mm_CNC; not fitted
R_DIV2: 10k; R_Axial_P7.62mm_CNC; not fitted

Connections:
/MOT_RAW: J_LOOM1.1, J_LOOM1.2, J_TEST1.3, R_DIV1.1
/TAP_OUT: C_FILT1.2, J_TEST1.2, R_DIV1.2, R_DIV2.2
GND: C_FILT1.1, J_TEST1.1, R_DIV2.1

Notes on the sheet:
CARVERA AIR CALIBRATION COUPON (25x20 mm SINGLE-SIDED B.Cu)
DIV4 MOTOR SENSE TEST CELL (30k / 10k + 100nF)

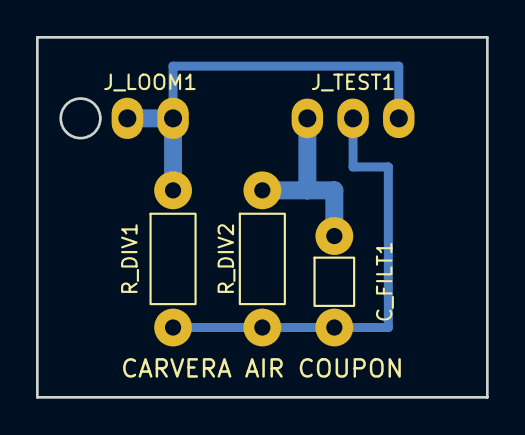
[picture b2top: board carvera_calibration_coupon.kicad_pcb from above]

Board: 2 copper layers, 25.0 x 20.0 mm, 5 parts (0 on the bottom side), 3 nets.

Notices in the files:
README.md:
License: Apache 2.0
